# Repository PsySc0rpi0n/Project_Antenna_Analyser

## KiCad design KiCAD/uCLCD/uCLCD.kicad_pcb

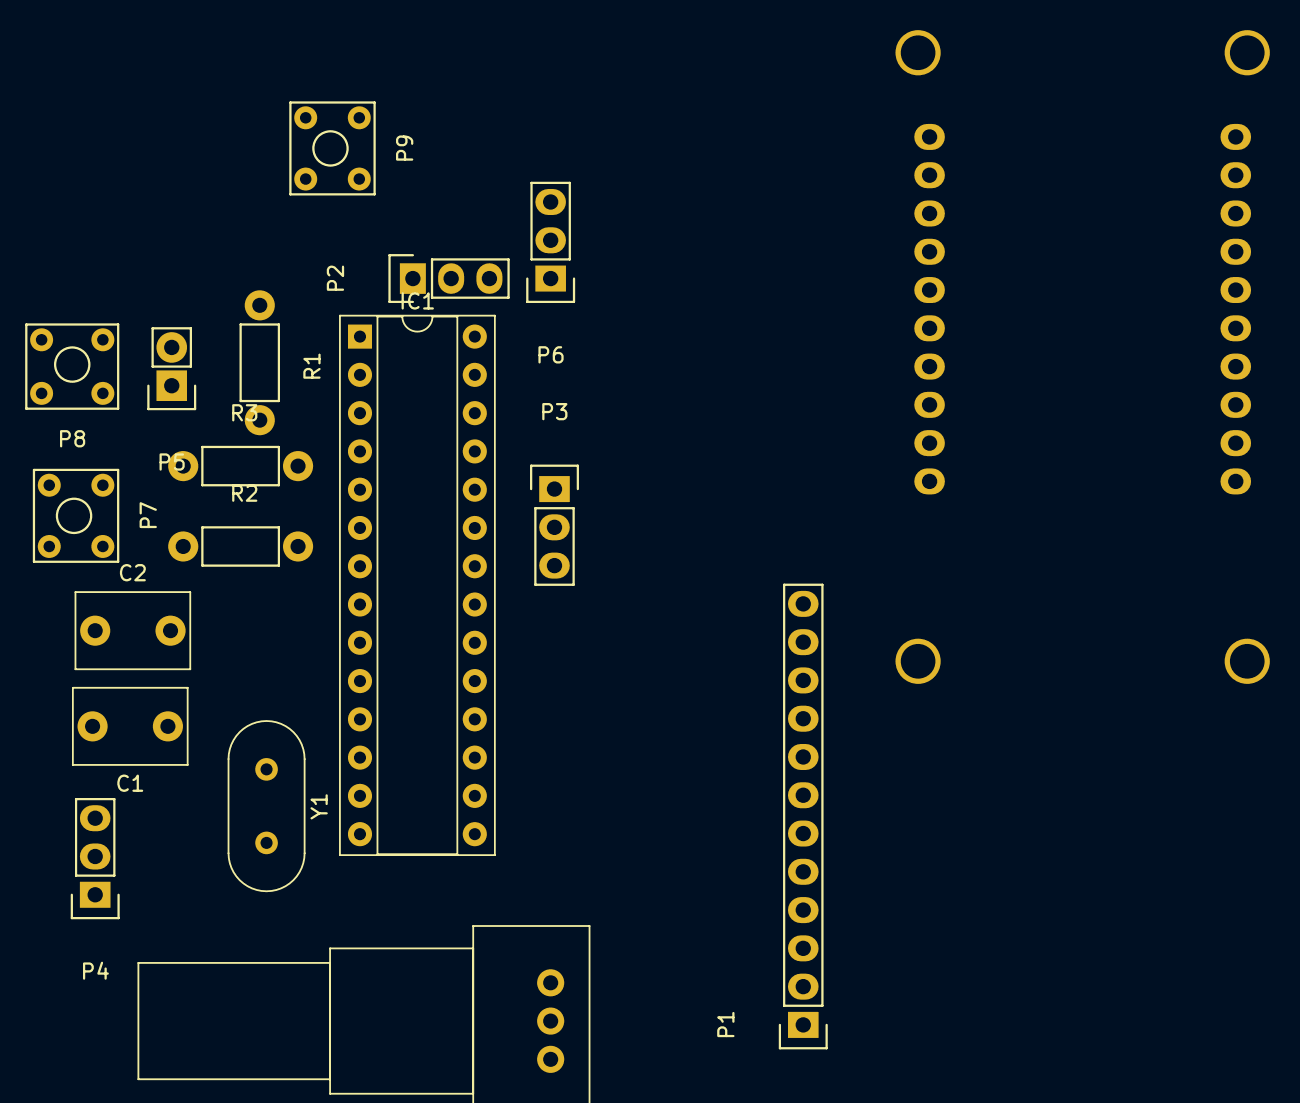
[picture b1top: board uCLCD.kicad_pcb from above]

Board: 2 copper layers, 18 parts (1 on the bottom side), 25 nets, no tracks yet.

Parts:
C1, C2: 22p; C_Disc_D7.5mm_W5.0mm_P5.00mm
IC1: ATMEGA328P-P; DIP-28_W7.62mm_Socket
P1: CONN_01X12; Socket_Strip_Straight_1x12
P2, P3, P4, P6: CONN_01X03; Pin_Header_Straight_1x03
P5: CONN_01X02; Pin_Header_Straight_1x02
P7, P8, P9: p_button
R1, R2, R3: 10k; Resistor_Horizontal_RM7mm
RV1: 10k; Potentiometer_VishaySpectrol_248GJ_249GJ_Vertical
U1: DDS; DDS9850
Y1: 16Mhz; Crystal_HC49-U_Vertical

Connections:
+5V: IC1.7, IC1.20, IC1.21, P1.1, P1.11, P5.1, R1.2, R2.2, R3.2, RV1.3, U1.1
GND: C1.2, C2.1, IC1.8, IC1.22, P1.2, P1.12, P2.3, P3.3, P4.1, P4.2, P4.3, P5.2, P6.1, P7.2, P8.2, P9.2, RV1.1, U1.6, U1.20
unnamed: C1.1, IC1.10, Y1.2
unnamed: C2.2, IC1.9, Y1.1
unnamed: IC1.1, P9.1, R1.1
unnamed: IC1.2, P2.1
unnamed: IC1.3, P2.2
unnamed: IC1.4, P8.1, R3.1
unnamed: IC1.5, P7.1, R2.1
unnamed: IC1.13, P1.5
unnamed: IC1.14, P1.4
unnamed: IC1.15, P1.6
unnamed: IC1.16, P1.7
unnamed: IC1.17, P1.8
unnamed: IC1.18, P1.9
unnamed: IC1.19, P1.10
unnamed: IC1.23, P3.2
unnamed: IC1.24, P3.1
unnamed: IC1.25, U1.2
unnamed: IC1.26, U1.3
unnamed: IC1.27, U1.4
unnamed: IC1.28, U1.5
unnamed: P1.3, RV1.2
unnamed: P6.2, U1.9
unnamed: P6.3, U1.10

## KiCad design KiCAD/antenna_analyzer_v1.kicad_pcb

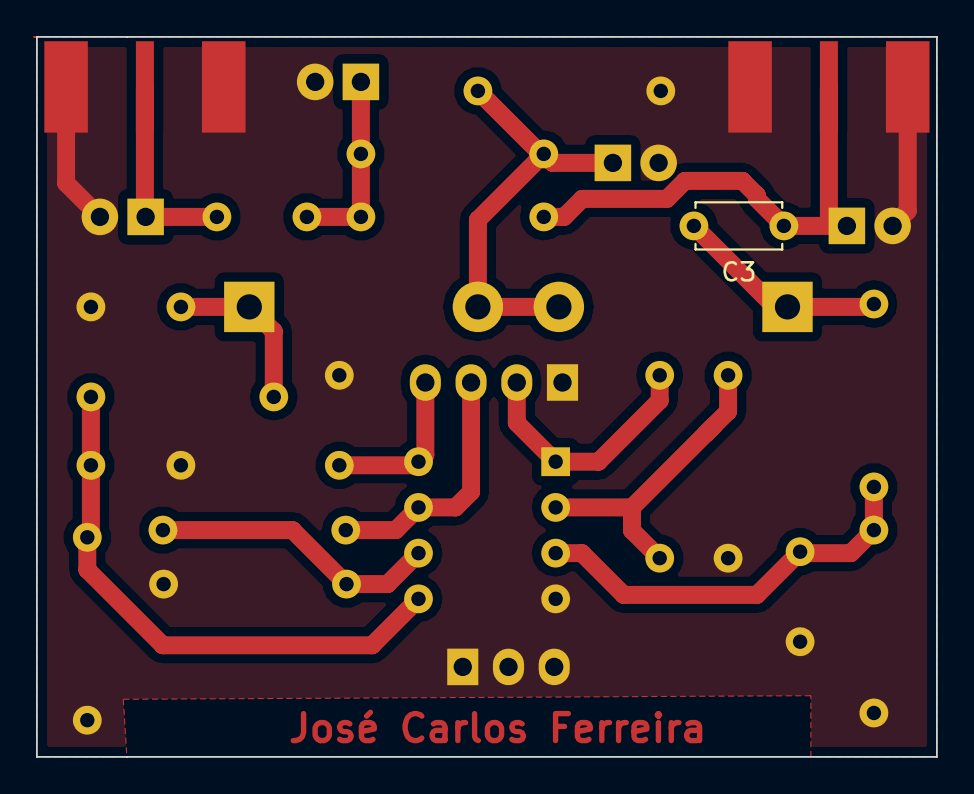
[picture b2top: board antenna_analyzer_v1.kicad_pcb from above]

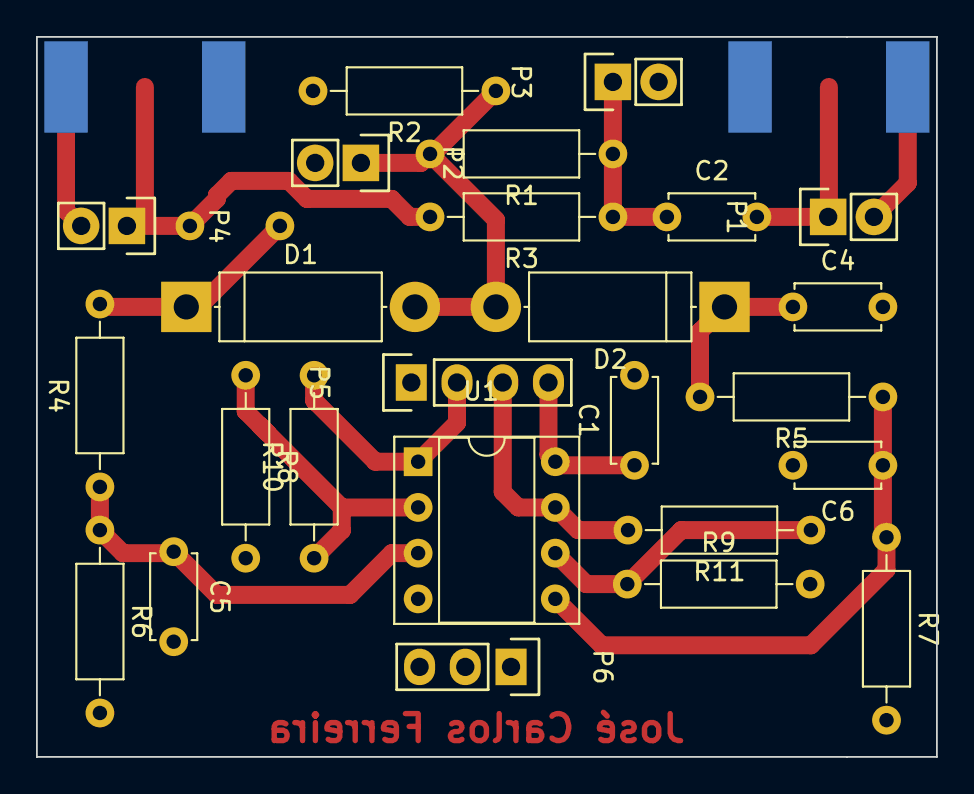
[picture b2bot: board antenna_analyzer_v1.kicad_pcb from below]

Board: 2 copper layers, 50.0 x 40.0 mm, 28 parts (25 on the bottom side), 14 nets.

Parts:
C1, C5, C6: 0.01u; C_Disc_D4.7mm_W2.5mm_P5.00mm
C2: 1u; C_Disc_D4.7mm_W2.5mm_P5.00mm
C3, C4: 0.1u; C_Disc_D4.7mm_W2.5mm_P5.00mm
D1, D2: D; D_5W_P12.70mm_Horizontal
J1: RFTEST; Molex_SMA_Jack_Edge_Mount
J2: DUT; Molex_SMA_Jack_Edge_Mount
P1, P2, P3, P4: CONN_01X02; Pin_Header_Straight_1x02
P5: CONN_01X04; Pin_Header_Straight_1x04
P6: CONN_01X03; Pin_Header_Straight_1x03
R1, R2, R3: 50; R_Axial_DIN0207_L6.3mm_D2.5mm_P10.16mm_Horizontal
R4, R5: 10k; R_Axial_DIN0207_L6.3mm_D2.5mm_P10.16mm_Horizontal
R6, R7: 100k; R_Axial_DIN0207_L6.3mm_D2.5mm_P10.16mm_Horizontal
R8, R9: 470; R_Axial_DIN0207_L6.3mm_D2.5mm_P10.16mm_Horizontal
R10, R11: 4.7k; R_Axial_DIN0207_L6.3mm_D2.5mm_P10.16mm_Horizontal
U1: MCP6002; DIP-8_W7.62mm_Socket

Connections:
+5V: C1.1, P5.4, U1.8
/Vfwd: P5.3, R11.2, U1.7
/Vrev: P5.2, R10.2, U1.1
GND: C1.2, C4.2, C5.2, C6.2, J1.2, J2.2, P1.2, P2.2, P3.2, P4.2, P5.1, P6.1, P6.2, P6.3, R2.2, R6.2, R7.2, R8.2, R9.2, U1.4
unnamed: C2.1, P3.1, R1.1, R3.1
unnamed: C2.2, J1.1, P1.1
unnamed: C3.1, J2.1, P4.1, R3.2
unnamed: C3.2, D1.1, R4.2
unnamed: C4.1, D2.1, R5.2
unnamed: C5.1, R4.1, R6.1, U1.3
unnamed: C6.1, R5.1, R7.1, U1.5
unnamed: D1.2, D2.2, P2.1, R1.2, R2.1
unnamed: R8.1, R10.1, U1.2
unnamed: R9.1, R11.1, U1.6

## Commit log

2017-09-05 fix adc voltage evaluation
2017-09-05 latest changes
2017-09-06 First test
2017-09-06 Next attemp for the whole code
2017-09-08 Changing strings to Program Space
2017-09-09 Deleting commented old code
2017-09-12 Replacing floating point values by integers only
2017-09-12 Replacing floating point by integers only
2017-09-12 Replacing floating point by integers only
    Post correction to vswr_value data type from unit8_t to uint16_t
2017-09-12 Fixing function prototypes
2017-09-12 Fixing LCD presentation
2017-09-15 Back to floating point calcs
2017-09-16 Adding push buttons code
2017-09-16 Adding push buttons code - extern keyword
2017-09-16 Adding push buttons code - extern keyword fix
2017-09-16 Adding push buttons code - fixing errors
2017-09-17 Error in frequncy sweep calculation fixed
2017-09-19 Fixing errors and uC setup pins
2017-09-19 Fixing errors in frequency update code
2017-09-21 Fixing bugs and adding frequency step down
2017-09-21 Fixing bugs and fixing ADC setup
2017-09-25 Changing the code and fixing bugs
2018-04-28 update old code
2018-05-13 Adding KiCAD folder
2018-05-13 Kicad files update
2018-05-13 folder update
2018-05-18 latest updates
2018-05-19 Latest changes to pcb files
2018-05-24 Circuit Schematic fixes
2018-05-26 Latest changes to 2nd pcb
2018-07-06 setting up timers
2018-07-10 Debunce code added
2018-07-10 removed pointer from current_freq_val
2018-07-18 Adding debounce code
2018-12-08 Last Makefile changes!
